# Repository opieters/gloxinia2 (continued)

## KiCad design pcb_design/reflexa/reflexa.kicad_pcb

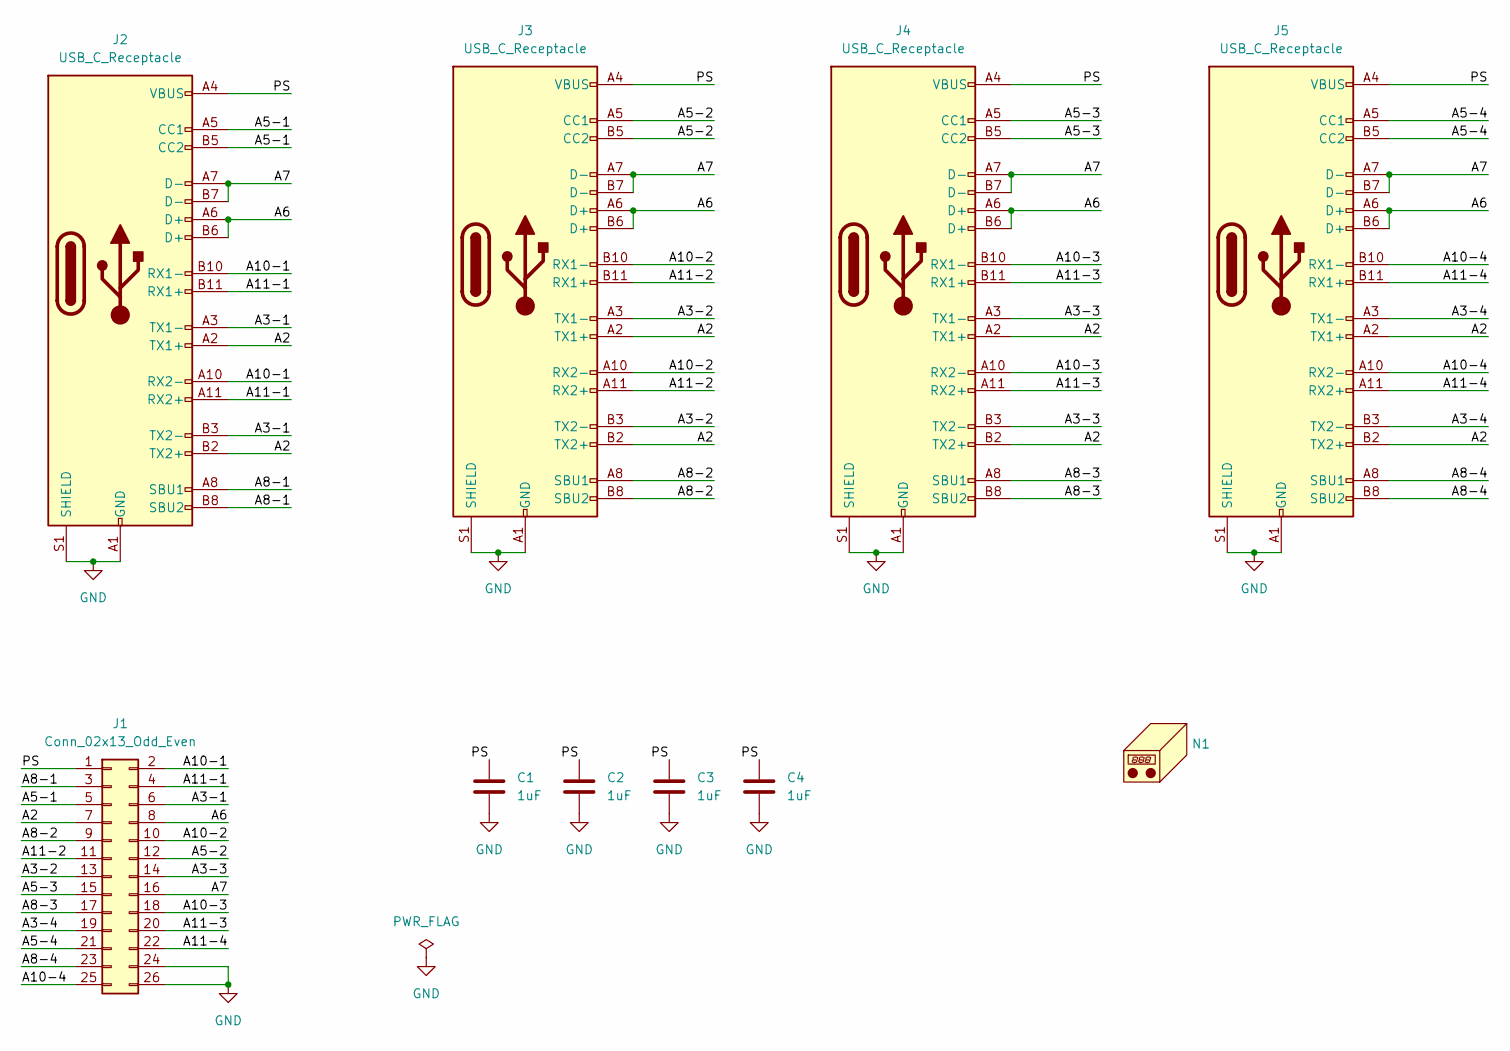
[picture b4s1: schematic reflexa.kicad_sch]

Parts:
C1, C2, C3, C4: 1uF; C_1206_3216Metric
J1: Conn_02x13_Odd_Even; PinHeader_2x13_P2.54mm_Vertical
J2, J3, J4, J5: USB_C_Receptacle; USB_C_Receptacle_Amphenol_12401861XX12A
N1: (no value)

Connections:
/A2: J1.7, J2.A2 (TX1+), J2.B2 (TX2+), J3.A2 (TX1+), J3.B2 (TX2+), J4.A2 (TX1+), J4.B2 (TX2+), J5.A2 (TX1+), J5.B2 (TX2+)
/A3-1: J1.6, J2.A3 (TX1-), J2.B3 (TX2-)
/A3-2: J1.13, J3.A3 (TX1-), J3.B3 (TX2-)
/A3-3: J1.14, J4.A3 (TX1-), J4.B3 (TX2-)
/A3-4: J1.19, J5.A3 (TX1-), J5.B3 (TX2-)
/A5-1: J1.5, J2.A5 (CC1), J2.B5 (CC2)
/A5-2: J1.12, J3.A5 (CC1), J3.B5 (CC2)
/A5-3: J1.15, J4.A5 (CC1), J4.B5 (CC2)
/A5-4: J1.21, J5.A5 (CC1), J5.B5 (CC2)
/A6: J1.8, J2.A6 (D+), J2.B6 (D+), J3.A6 (D+), J3.B6 (D+), J4.A6 (D+), J4.B6 (D+), J5.A6 (D+), J5.B6 (D+)
/A7: J1.16, J2.A7 (D-), J2.B7 (D-), J3.A7 (D-), J3.B7 (D-), J4.A7 (D-), J4.B7 (D-), J5.A7 (D-), J5.B7 (D-)
/A8-1: J1.3, J2.A8 (SBU1), J2.B8 (SBU2)
/A8-2: J1.9, J3.A8 (SBU1), J3.B8 (SBU2)
/A8-3: J1.17, J4.A8 (SBU1), J4.B8 (SBU2)
/A8-4: J1.23, J5.A8 (SBU1), J5.B8 (SBU2)
/A10-1: J1.2, J2.A10 (RX2-), J2.B10 (RX1-)
/A10-2: J1.10, J3.A10 (RX2-), J3.B10 (RX1-)
/A10-3: J1.18, J4.A10 (RX2-), J4.B10 (RX1-)
/A10-4: J1.25, J5.A10 (RX2-), J5.B10 (RX1-)
/A11-1: J1.4, J2.A11 (RX2+), J2.B11 (RX1+)
/A11-2: J1.11, J3.A11 (RX2+), J3.B11 (RX1+)
/A11-3: J1.20, J4.A11 (RX2+), J4.B11 (RX1+)
/A11-4: J1.22, J5.A11 (RX2+), J5.B11 (RX1+)
/PS: C1.1, C2.1, C3.1, C4.1, J1.1, J2.A4 (VBUS), J2.A9 (VBUS), J2.B4 (VBUS), J2.B9 (VBUS), J3.A4 (VBUS), J3.A9 (VBUS), J3.B4 (VBUS), J3.B9 (VBUS), J4.A4 (VBUS), J4.A9 (VBUS), J4.B4 (VBUS), J4.B9 (VBUS), J5.A4 (VBUS), J5.A9 (VBUS), J5.B4 (VBUS), J5.B9 (VBUS)
GND: C1.2, C2.2, C3.2, C4.2, J1.24, J1.26, J2.A1 (GND), J2.A12 (GND), J2.B1 (GND), J2.B12 (GND), J2.S1 (SHIELD), J3.A1 (GND), J3.A12 (GND), J3.B1 (GND), J3.B12 (GND), J3.S1 (SHIELD), J4.A1 (GND), J4.A12 (GND), J4.B1 (GND), J4.B12 (GND), J4.S1 (SHIELD), J5.A1 (GND), J5.A12 (GND), J5.B1 (GND), J5.B12 (GND), J5.S1 (SHIELD)

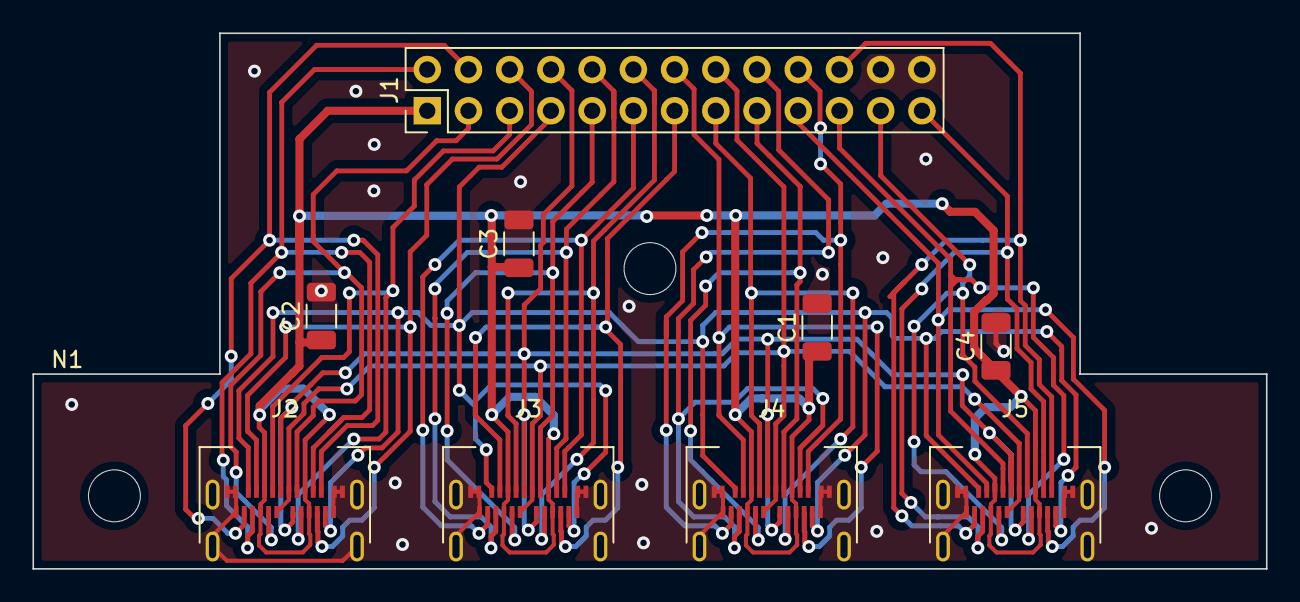
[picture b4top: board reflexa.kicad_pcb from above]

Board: 2 copper layers, 76.0 x 33.0 mm, 10 parts (0 on the bottom side), 25 nets.
